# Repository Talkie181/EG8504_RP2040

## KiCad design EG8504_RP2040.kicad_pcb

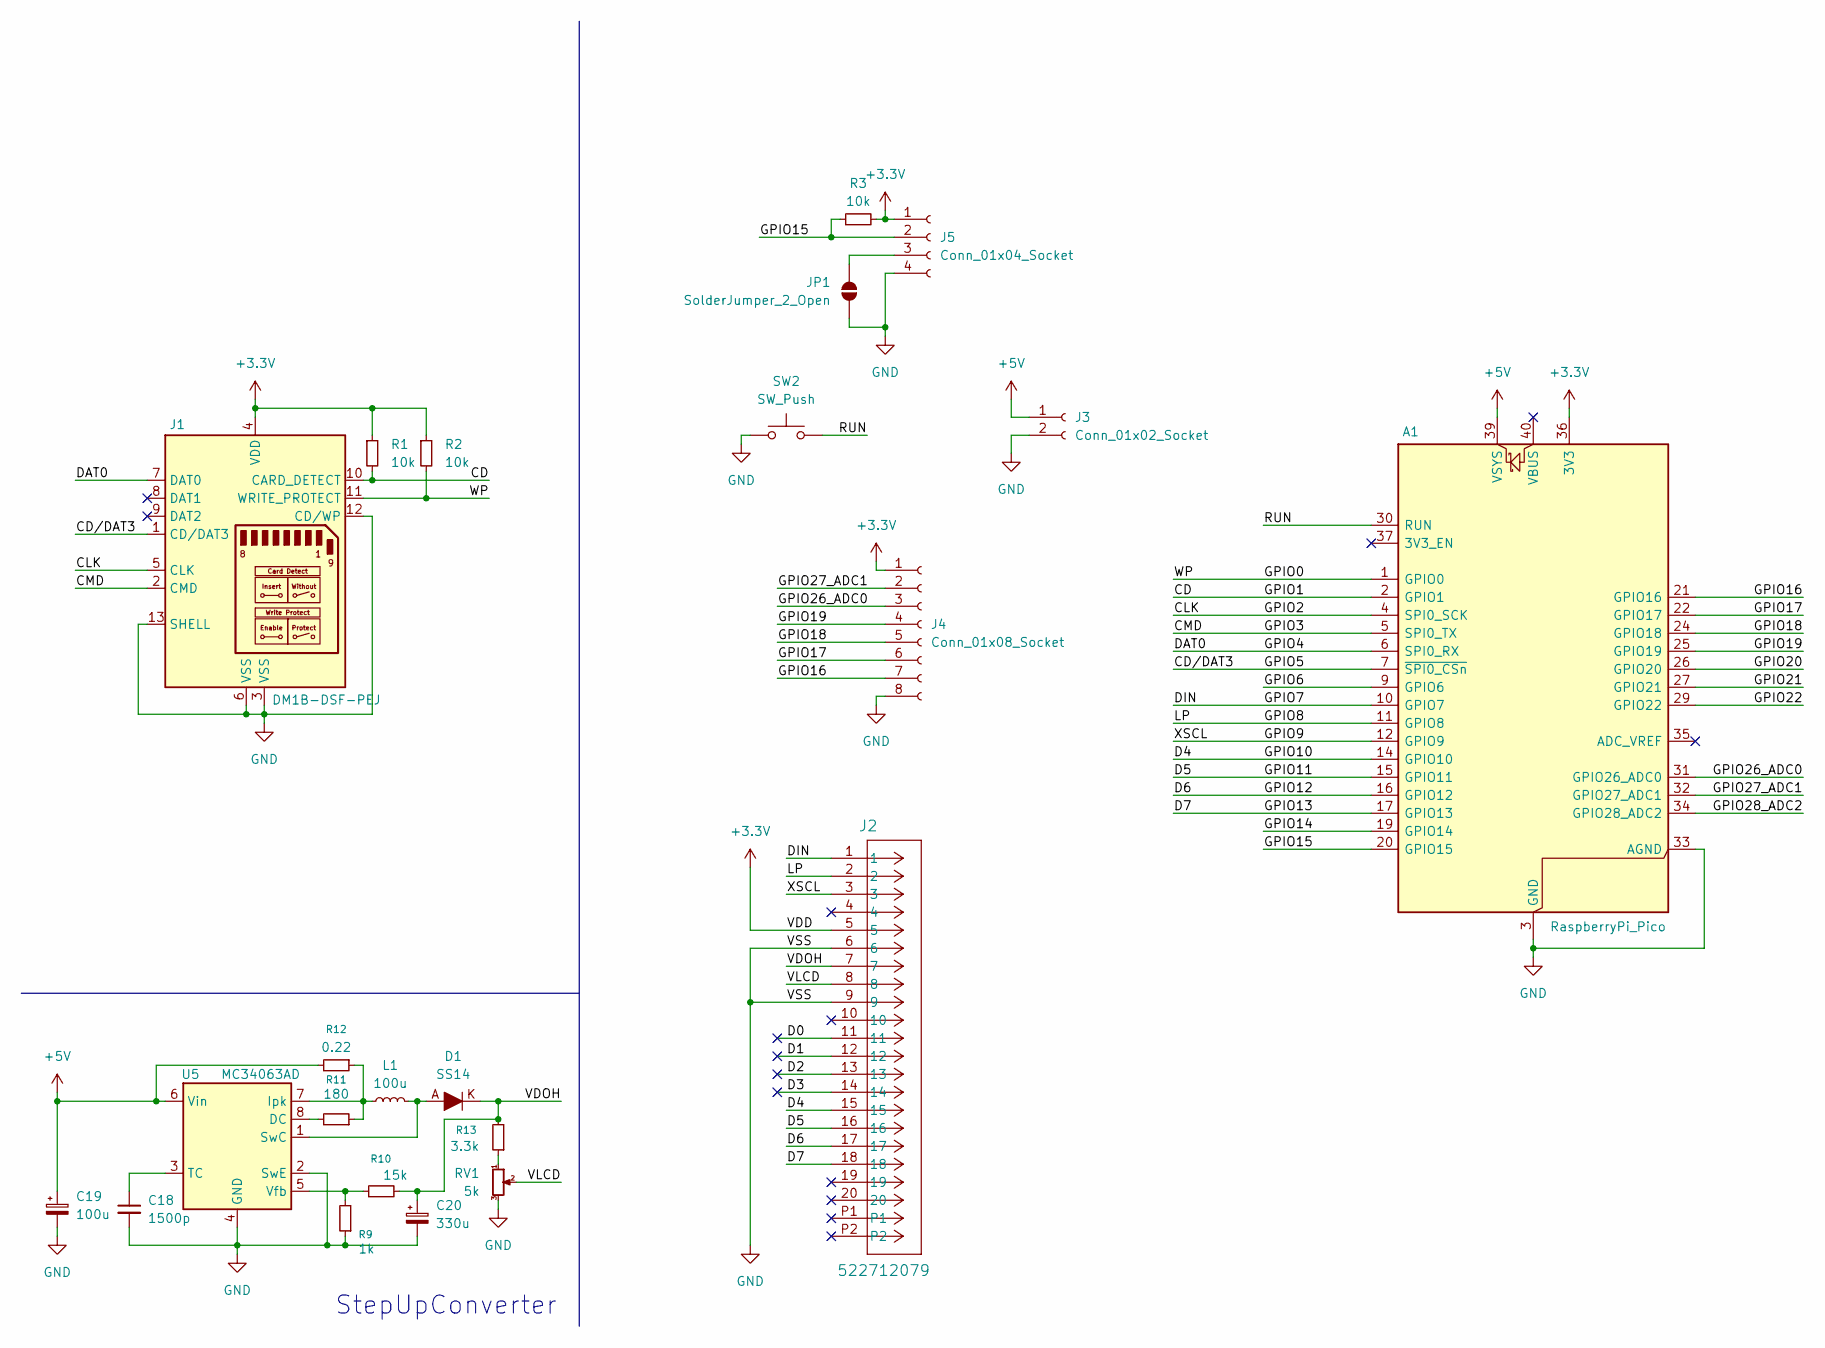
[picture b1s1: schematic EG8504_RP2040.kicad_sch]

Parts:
A1: RaspberryPi_Pico; RaspberryPi_Pico_Common_THT
C18: 1500p; C_0603_1608Metric_Pad1.08x0.95mm_HandSolder
C19: 100u; CP_Elec_6.3x5.4
C20: 330u; CP_Elec_10x10.5
D1: SS14; DO-214AC; MPN SS14; Digi-Key_PN SS14CT-ND
J1: DM1B-DSF-PEJ
J2: 522712079; CON_522712079_MOL
J3: Conn_01x02_Socket; JST_XH_B2B-XH-A_1x02_P2.50mm_Vertical
J4: Conn_01x08_Socket; JST_XH_B8B-XH-A_1x08_P2.50mm_Vertical
J5: Conn_01x04_Socket; JST_XH_B4B-XH-A_1x04_P2.50mm_Vertical
JP1: SolderJumper_2_Open; SolderJumper-2_P1.3mm_Open_RoundedPad1.0x1.5mm
L1: 100u; L_Taiyo-Yuden_NR-10050_9.8x10.0mm_HandSoldering
R1, R2, R3: 10k; R_0603_1608Metric_Pad0.98x0.95mm_HandSolder
R9: 1k; R_Axial_DIN0207_L6.3mm_D2.5mm_P7.62mm_Horizontal
R10: 15k; R_Axial_DIN0207_L6.3mm_D2.5mm_P7.62mm_Horizontal
R11: 180; R_Axial_DIN0207_L6.3mm_D2.5mm_P7.62mm_Horizontal
R12: 0.22; R_Axial_DIN0207_L6.3mm_D2.5mm_P7.62mm_Horizontal
R13: 3.3k; R_Axial_DIN0207_L6.3mm_D2.5mm_P7.62mm_Horizontal
RV1: 5k; Potentiometer_Vishay_T73YP_Vertical
SW2: SW_Push; SW_Push_1P1T_NO_Vertical_Wuerth_434133025816
U5: MC34063AD; SOIC-8_3.9x4.9mm_P1.27mm

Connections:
+3.3V: A1.36 (3V3), J1.4 (VDD), J2.5, J4.1, J5.1, R1.1, R2.1, R3.2
+5V: A1.39 (VSYS), C19.1, J3.1, R12.2, U5.6 (Vin)
/CD: A1.2 (GPIO1), J1.10 (CARD_DETECT), R1.2
/CD/DAT3: A1.7 (~SPI0_CSn), J1.1 (CD/DAT3)
/CLK: A1.4 (SPI0_SCK), J1.5 (CLK)
/CMD: A1.5 (SPI0_TX), J1.2 (CMD)
/D0: J2.11
/D1: J2.12
/D2: J2.13
/D3: J2.14
/D4: A1.14 (GPIO10), J2.15
/D5: A1.15 (GPIO11), J2.16
/D6: A1.16 (GPIO12), J2.17
/D7: A1.17 (GPIO13), J2.18
/DAT0: A1.6 (SPI0_RX), J1.7 (DAT0)
/DIN: A1.10 (GPIO7), J2.1
/GPIO0: A1.1 (GPIO0), J1.11 (WRITE_PROTECT), R2.2
/GPIO6: A1.9 (GPIO6)
/GPIO8: A1.11 (GPIO8), J2.2
/GPIO9: A1.12 (GPIO9), J2.3
/GPIO14: A1.19 (GPIO14)
/GPIO15: A1.20 (GPIO15), J5.2, R3.1
/GPIO16: A1.21 (GPIO16), J4.7
/GPIO17: A1.22 (GPIO17), J4.6
/GPIO18: A1.24 (GPIO18), J4.5
/GPIO19: A1.25 (GPIO19), J4.4
/GPIO20: A1.26 (GPIO20)
/GPIO21: A1.27 (GPIO21)
/GPIO22: A1.29 (GPIO22)
/GPIO26_ADC0: A1.31 (GPIO26_ADC0), J4.3
/GPIO27_ADC1: A1.32 (GPIO27_ADC1), J4.2
/GPIO28_ADC2: A1.34 (GPIO28_ADC2)
/RUN: A1.30 (RUN), SW2.2
/VDOH: C20.1, D1.K, J2.7, R10.2, R13.2
/VLCD: J2.8, RV1.2
GND: A1.3 (GND), A1.8 (GND), A1.13 (GND), A1.18 (GND), A1.23 (GND), A1.28 (GND), A1.33 (AGND), A1.38 (GND), C18.2, C19.2, C20.2, J1.3 (VSS), J1.6 (VSS), J1.12 (CD/WP), J1.13 (SHELL), J2.6, J2.9, J3.2, J4.8, J5.4, JP1.2 (B), R9.1, RV1.3, SW2.1, U5.2 (SwE), U5.4 (GND)
unnamed: J5.3, JP1.1 (A)
unnamed: R13.1, RV1.1
unnamed: R11.2, U5.8 (DC)
unnamed: L1.1, R11.1, R12.1, U5.7 (Ipk)
unnamed: D1.A, L1.2, U5.1 (SwC)
unnamed: C18.1, U5.3 (TC)
unnamed: R9.2, R10.1, U5.5 (Vfb)

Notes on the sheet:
StepUpConverter

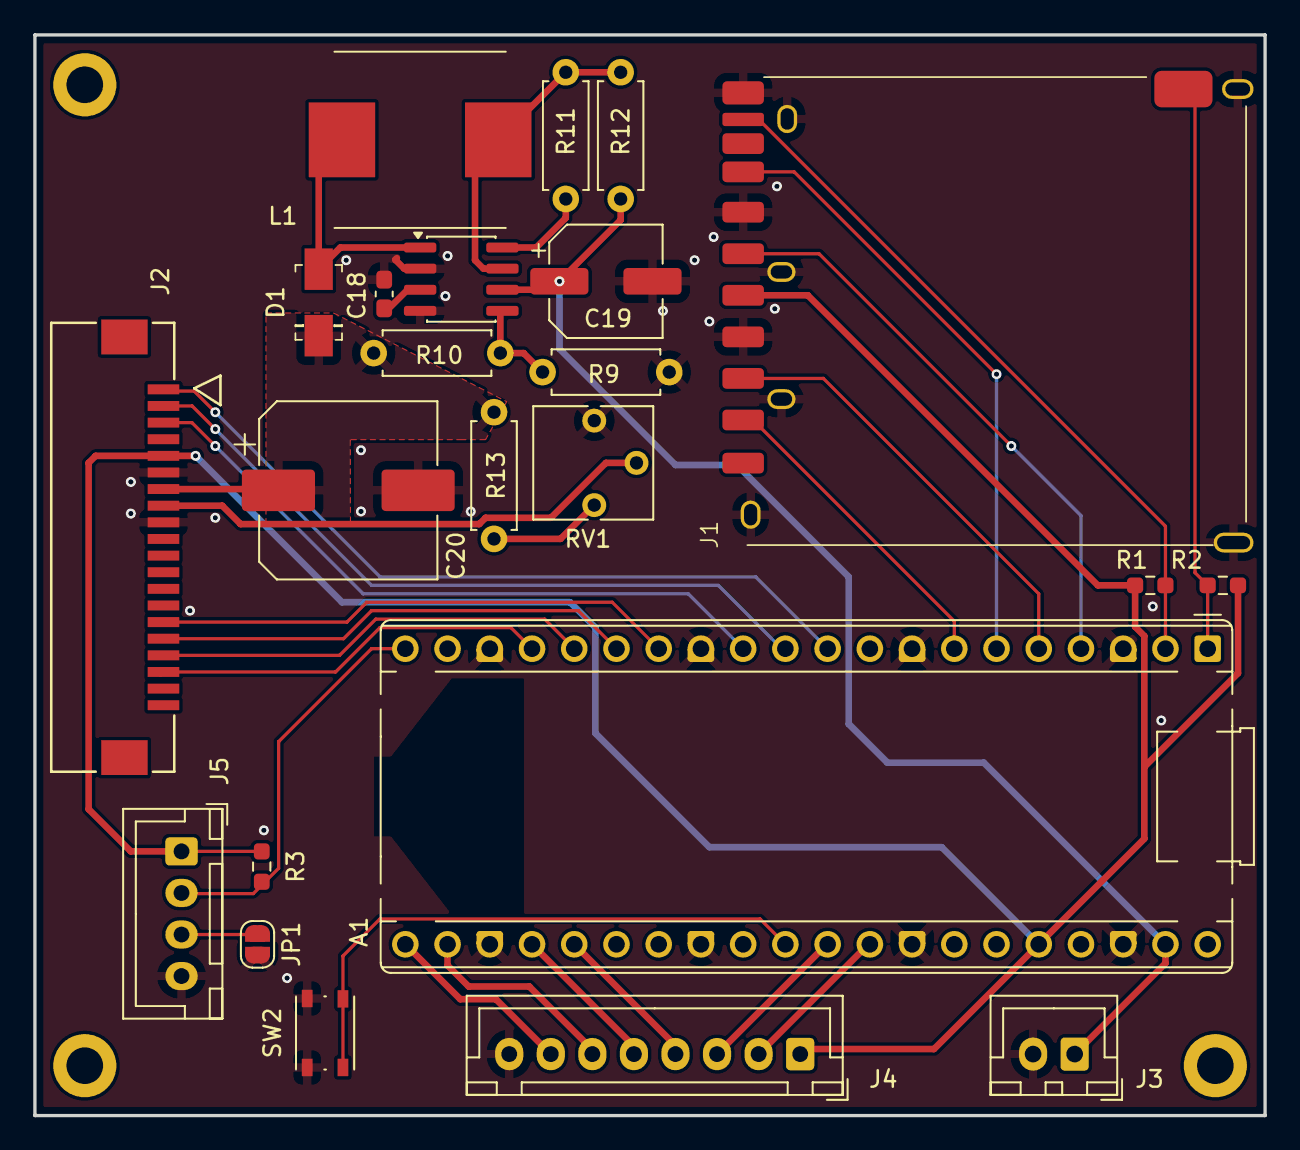
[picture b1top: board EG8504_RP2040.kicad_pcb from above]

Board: 2 copper layers, 74.0 x 65.0 mm, 23 parts (0 on the bottom side), 33 nets.

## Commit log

2025-11-07 rp2040
2025-11-09 rp2040周りの部品配線を追加
2025-11-10 EG8504用のDCDCを追加
2025-11-11 コネクタの配置とPCB
2025-11-12 マイコン回りの配線
2025-11-16 rp2040からpicoに変更
2025-11-16 sd入れたpsb
2025-11-17 sdの向き違った
2025-11-18 シルクの修正
2025-11-25 DHT11を追加
2025-11-30 スルーホール抵抗に
